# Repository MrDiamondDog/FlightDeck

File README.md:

# FlightDeck

Show your overhead flights in a nice and large LED matrix! Perfect addition to any room, especially to those nearby airports.

Additionally, the matrix will be able to display whatever you want in sleep/home states (when there are no flights), all customizable via a webserver hosted on the ESP, including displaying custom APIs!

I've seen a couple projects like this, and thought it would provide some nice experience to make my own, and it fits perfectly for Hack Club's Blueprint YSWS!

I haven't looked at any other similar projects, I want to build my own without copying others.

## Hardware

A custom PCB is required for this project to connect the ESP dev board to the LED matrix.
All the gerber and KiCad files are in the `pcb` folder, and should run you about $5 on JLCPCB.

The rest of the hardware falls around $35 total on Aliexpress. See the [BOM](BOM) below.

- 64x32 RGB LED Matrix, 5mm pitch, 320x160mm ([Aliexpress](https://www.aliexpress.us/item/2251832185365664.html?spm=a2g0o.cart.0.0.2e4d38da3nXc6x&mp=1&pdp_npi=6%40dis%21USD%21USD%2012.49%21USD%2012.49%21%21USD%2012.49%21%21%21%402103126e17682735896398074e7fd6%2157993804537%21ct%21US%216602055344%21%211%210%21&gatewayAdapt=glo2usa#nav-specification))
- ESP32-DevKitC V4 Devboard ([Aliexpress](https://www.aliexpress.us/item/3256808703088919.html?spm=a2g0o.detail.0.0.5140gswugswudo&mp=1&pdp_npi=6%40dis%21USD%21USD%208.58%21USD%208.58%21%21USD%208.58%21%21%21%4021030a4b17682769544637132ef6ef%2112000047093672778%21ct%21US%216602055344%21%211%210%21&gatewayAdapt=glo2usa))
- 2x8 Through-hole Female Pin Socket ([Aliexpress](https://www.aliexpress.us/item/3256803911413457.html?spm=a2g0o.detail.0.0.f165asKbasKbNN&mp=1&pdp_npi=6%40dis%21USD%21USD%204.79%21USD%203.85%21%21USD%203.85%21%21%21%402101eede17682773036007831e7bf5%2112000028025434755%21ct%21US%216602055344%21%211%210%21&gatewayAdapt=glo2usa)) (only available in 10 pack) 
- 2.1mm Terminal Block Adapter ([Aliexpress](https://www.aliexpress.us/item/3256806569458868.html?spm=a2g0o.productlist.0.0.1448c50c2Ocu5n&mp=1&pdp_npi=6%40dis%21USD%21USD%204.07%21USD%203.91%21%21USD%203.91%21%21%21%402103126e17682742270461949e7fd6%2112000038197813479%21ct%21US%216602055344%21%211%210%21&gatewayAdapt=glo2usa](https://www.aliexpress.us/item/3256806079081322.html?spm=a2g0o.cart.similar_items.1.4c2938da4WRVyR&utparam-url=scene%3Aimage_search%7Cquery_from%3Acart_normal_item%7Cx_object_id%3A1005006265396074%7C_p_origin_prod%3A&algo_pvid=84213d49-7822-45b7-86d6-2cbb8091ce92&algo_exp_id=84213d49-7822-45b7-86d6-2cbb8091ce92&pdp_ext_f=%7B%22order%22%3A%223742%22%2C%22fromPage%22%3A%22search%22%7D&pdp_npi=6%40dis%21USD%213.89%211.99%21%21%2126.98%2113.82%21%40210319b017683292512364683ef193%2112000036535453252%21sea%21US%216602055344%21X%211%210%21n_tag%3A-29911%3Bd%3A92c261d9%3Bm03_new_user%3A-29895%3BpisId%3A5000000198192865&gatewayAdapt=4itemAdapt))) (only in 5 pack)
- 5V 4A Barrel Jack Power Supply ([Aliexpress](https://www.aliexpress.us/item/3256807146253605.html?spm=a2g0o.cart.0.0.1e5c38daCS0svQ&mp=1&pdp_npi=6%40dis%21USD%21USD%2011.26%21USD%2010.67%21%21USD%2010.67%21%21%21%402101ea8c17682799562916428e3d0e%2112000040414863406%21ct%21US%216602055344%21%211%210%21&gatewayAdapt=glo2usa](https://www.aliexpress.us/item/3256806800927492.html?spm=a2g0o.cart.similar_items.3.4c2938dam4DysV&utparam-url=scene%3Aimage_search%7Cquery_from%3Acart_normal_item%7Cx_object_id%3A1005006987242244%7C_p_origin_prod%3A&algo_pvid=6da0179e-90c3-45d4-a35c-01e6f266bc89&algo_exp_id=6da0179e-90c3-45d4-a35c-01e6f266bc89&pdp_ext_f=%7B%22order%22%3A%22617%22%2C%22fromPage%22%3A%22search%22%7D&pdp_npi=6%40dis%21USD%213.38%212.48%21%21%2123.41%2117.16%21%40210319b017683291228331371ef193%2112000038965797747%21sea%21US%216602055344%21X%211%210%21n_tag%3A-29911%3Bd%3A92c261d9%3Bm03_new_user%3A-29895%3BpisId%3A5000000198192865&gatewayAdapt=4itemAdapt)))

### PCB

The PCB is pretty simple, just a bunch of holes for the ESP and HUB75 connector. 
There are extra holes along the ESP in case of emergency jumper wiring.

### Wiring

1. Solder the dev board into the PCB. The PCB should have silkscreen text where you are putting the board. The USB should be hanging off the edge slightly.

2. Solder the pin connectors on the BACK of the PCB (opposite side of the dev board)

3. Insert the PCB into the back of the LED matrix, making sure that the one you are plugging into is the INPUT (on the left), not the OUTPUT connector.

4. Connect the included power cables to the back of the LED matrix, then plug the U shaped ends into the (female) terminal block adapters, like so

5. Plug in your power supply to the adapter
6. Plug in micro USB to the esp

## Firmware

Programmed in CircuitPython, using the https://airlabs.co/ free live flight API. You may have to send them an email to get access. 

Make sure to rename the `settings.example.toml` file to `settings.toml` and fill in all the values.

TODO: There will be a webserver to customize the panel with, including custom sleep/home screens and custom API connections.

## BOM

**Please note: some of these items are only available in packs of 10 or 5, I could not find a cheaper alternative.**

| Name |Description | Link | Cost | Quantity | Total Price |
| ---- | --- | --- | --- | --- | --- |
| Factory P5 Indoor 320mmx160mm 16 Scan SMD Full Color Module 64x32 Pixels Dot Matrix Panel Video Screen Board | 64x32 LED Matrix | [Aliexpress](https://www.aliexpress.us/item/2251832185365664.html?spm=a2g0o.cart.0.0.64d038dauBZnYy&mp=1&pdp_npi=6%40dis%21USD%21USD%2012.49%21USD%2011.69%21%21USD%2011.69%21%21%21%402103128917674129797053573ecebd%2157993804537%21ct%21US%216602055344%21%211%210%21&gatewayAdapt=glo2usa) | $11.69 | 1 | $11.69 |
| ESP32-DevKitC V4 core board ESP32 development board All Types with ESP32-WROOM-32 32D 32U 32E WIFI+Bluetooth IoT NodeMCU-32 | ESP32-DevKitC V4 Dev Board | [Aliexpress](https://www.aliexpress.us/item/3256808703088919.html?spm=a2g0o.cart.0.0.2c9538dayiBd5T&mp=1&pdp_npi=6%40dis%21USD%21USD%208.58%21USD%208.58%21%21USD%208.58%21%21%21%402103126e17682743226734291e7fd6%2112000047093672778%21ct%21US%216602055344%21%211%210%21&gatewayAdapt=glo2usa) | $7.78 | 1 | $7.78 |
| 10PCS 2.54mm Double Row Female Long Pin 11mm Breakaway PCB Board Pin Header Socket Connector 2x8 pins | 2x8 Through-hole Female Pin Sockets (10pcs) | [Aliexpress](https://www.aliexpress.us/item/3256803911413457.html?spm=a2g0o.cart.0.0.2c9538dayiBd5T&mp=1&pdp_npi=6%40dis%21USD%21USD%204.79%21USD%203.85%21%21USD%203.85%21%21%21%402103126e17682743226734291e7fd6%2112000028025434755%21ct%21US%216602055344%21%211%210%21&gatewayAdapt=glo2usa) | $3.85 | 1 | $3.85 |
| 5pcs DC 12V Female And Male Connectors 5.5x2.1mm Power Plug Adapter Jacks Sockets For Signal Color LED Strip Light CCTV Camera | 2.1mm Terminal Block Adapter (5pcs) | [Aliexpress](https://www.aliexpress.us/item/3256806079081322.html?spm=a2g0o.cart.similar_items.1.4c2938da4WRVyR&utparam-url=scene%3Aimage_search%7Cquery_from%3Acart_normal_item%7Cx_object_id%3A1005006265396074%7C_p_origin_prod%3A&algo_pvid=84213d49-7822-45b7-86d6-2cbb8091ce92&algo_exp_id=84213d49-7822-45b7-86d6-2cbb8091ce92&pdp_ext_f=%7B%22order%22%3A%223742%22%2C%22fromPage%22%3A%22search%22%7D&pdp_npi=6%40dis%21USD%213.89%211.99%21%21%2126.98%2113.82%21%40210319b017683292512364683ef193%2112000036535453252%21sea%21US%216602055344%21X%211%210%21n_tag%3A-29911%3Bd%3A92c261d9%3Bm03_new_user%3A-29895%3BpisId%3A5000000198192865&gatewayAdapt=4itemAdapt) | $1.83 | 1 | $1.83 |
| DC 5V LED Power Supply AC 110V~220V Lighting Transformer 4A Power Adapters For CCTV Camera Router | 5V 4A Power Supply | [Aliexpress](https://www.aliexpress.us/item/3256806800927492.html?spm=a2g0o.cart.similar_items.3.4c2938dam4DysV&utparam-url=scene%3Aimage_search%7Cquery_from%3Acart_normal_item%7Cx_object_id%3A1005006987242244%7C_p_origin_prod%3A&algo_pvid=6da0179e-90c3-45d4-a35c-01e6f266bc89&algo_exp_id=6da0179e-90c3-45d4-a35c-01e6f266bc89&pdp_ext_f=%7B%22order%22%3A%22617%22%2C%22fromPage%22%3A%22search%22%7D&pdp_npi=6%40dis%21USD%213.38%212.48%21%21%2123.41%2117.16%21%40210319b017683291228331371ef193%2112000038965797747%21sea%21US%216602055344%21X%211%210%21n_tag%3A-29911%3Bd%3A92c261d9%3Bm03_new_user%3A-29895%3BpisId%3A5000000198192865&gatewayAdapt=4itemAdapt) | $5.18 | 1 | $5.18 |
| JLCPCB Order (5 PCBs) | PCB |  | $3.12 | 1 | $3.12 |
| Total |  |  |  |  | $37.13 |

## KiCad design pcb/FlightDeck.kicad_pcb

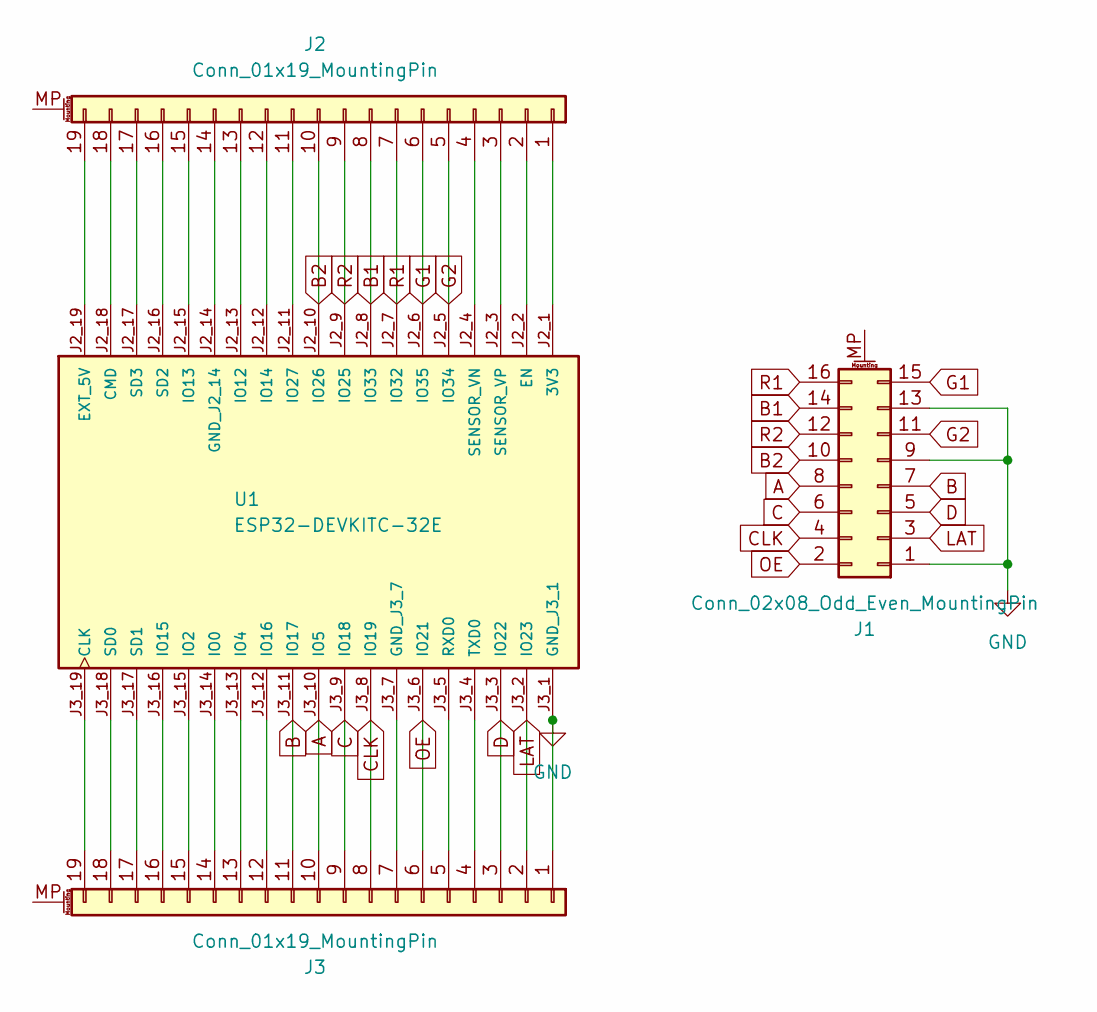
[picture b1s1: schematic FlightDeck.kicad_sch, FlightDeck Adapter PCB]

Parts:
J1: Conn_02x08_Odd_Even_MountingPin; PinSocket_2x08_P2.54mm_Vertical
J2, J3: Conn_01x19_MountingPin; PinSocket_1x19_P2.54mm_Vertical
U1: ESP32-DEVKITC-32E; MODULE_ESP32-DEVKITC-32E; PARTREV 1.4

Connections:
A: J1.8, J3.10, U1.J3_10 (IO5)
B: J1.7, J3.11, U1.J3_11 (IO17)
B1: J1.14, J2.8, U1.J2_8 (IO33)
B2: J1.10, J2.10, U1.J2_10 (IO26)
C: J1.6, J3.9, U1.J3_9 (IO18)
CLK: J1.4, J3.8, U1.J3_8 (IO19)
D: J1.5, J3.3, U1.J3_3 (IO22)
G1: J1.15, J2.6, U1.J2_6 (IO35)
G2: J1.11, J2.5, U1.J2_5 (IO34)
GND: J1.1, J1.9, J1.13, J3.1, U1.J3_1 (GND_J3_1)
LAT: J1.3, J3.2, U1.J3_2 (IO23)
unnamed: J2.1, U1.J2_1 (3V3)
unnamed: J2.2, U1.J2_2 (EN)
unnamed: J2.3, U1.J2_3 (SENSOR_VP)
unnamed: J2.4, U1.J2_4 (SENSOR_VN)
unnamed: J2.11, U1.J2_11 (IO27)
unnamed: J2.12, U1.J2_12 (IO14)
unnamed: J2.13, U1.J2_13 (IO12)
unnamed: J2.14, U1.J2_14 (GND_J2_14)
unnamed: J2.15, U1.J2_15 (IO13)
unnamed: J2.16, U1.J2_16 (SD2)
unnamed: J2.17, U1.J2_17 (SD3)
unnamed: J2.18, U1.J2_18 (CMD)
unnamed: J2.19, U1.J2_19 (EXT_5V)
unnamed: J3.4, U1.J3_4 (TXD0)
unnamed: J3.5, U1.J3_5 (RXD0)
unnamed: J3.7, U1.J3_7 (GND_J3_7)
unnamed: J3.12, U1.J3_12 (IO16)
unnamed: J3.13, U1.J3_13 (IO4)
unnamed: J3.14, U1.J3_14 (IO0)
unnamed: J3.15, U1.J3_15 (IO2)
unnamed: J3.16, U1.J3_16 (IO15)
unnamed: J3.17, U1.J3_17 (SD1)
unnamed: J3.18, U1.J3_18 (SD0)
unnamed: J3.19, U1.J3_19 (CLK)
OE: J1.2, J3.6, U1.J3_6 (IO21)
R1: J1.16, J2.7, U1.J2_7 (IO32)
R2: J1.12, J2.9, U1.J2_9 (IO25)

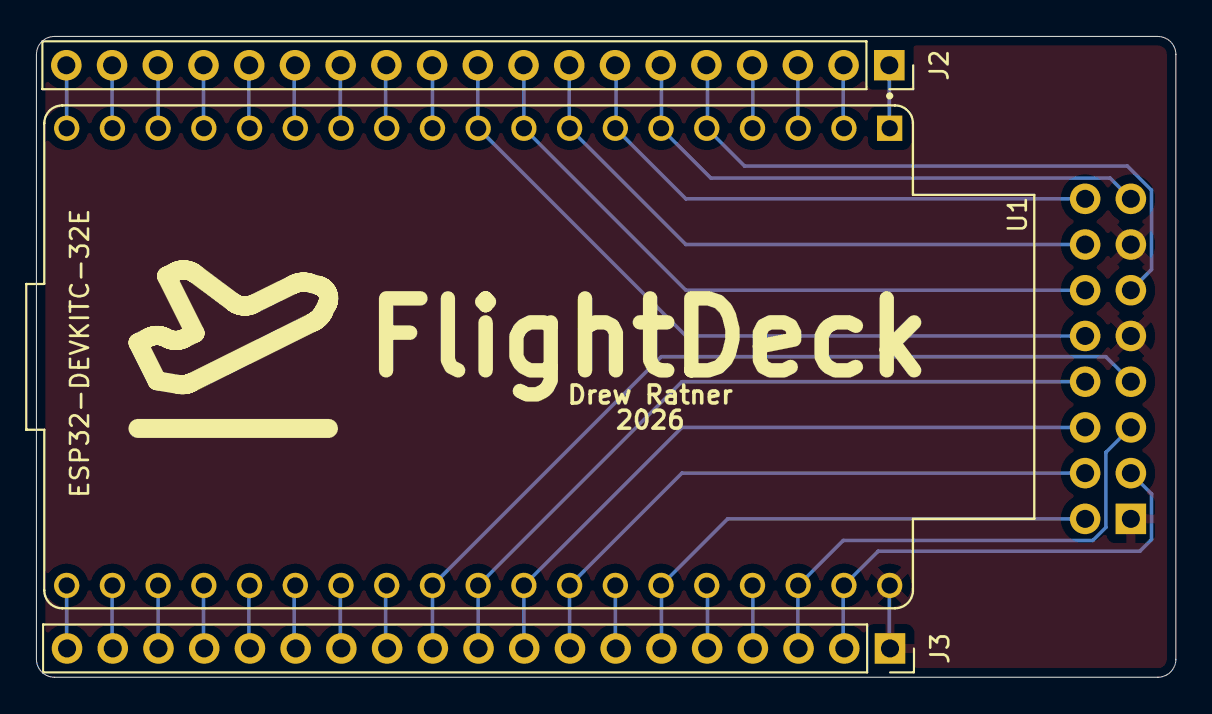
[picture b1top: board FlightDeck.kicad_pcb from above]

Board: 2 copper layers, 63.3 x 35.6 mm, 4 parts (1 on the bottom side), 38 nets.

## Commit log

2026-01-03 Init
2026-01-04 New firmware
2026-01-04 Update CAD and images with mounting holes
2026-01-13 New PCB
2026-01-13 New PCB and hardware details
2026-01-13 Update BOM
2026-01-13 CAD Upload
2026-01-13 Update readme with JLCPCB cart image and accurate PCB price
2026-01-13 Price Optimization
2026-01-13 Update PCB with silkscreen
2026-02-02 Updated firmware to not use circuitpython
2026-02-02 Don't commit wifi.hpp anymore
